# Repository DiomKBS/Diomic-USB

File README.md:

# Diomic-USB
A microphone for all the audiophiles

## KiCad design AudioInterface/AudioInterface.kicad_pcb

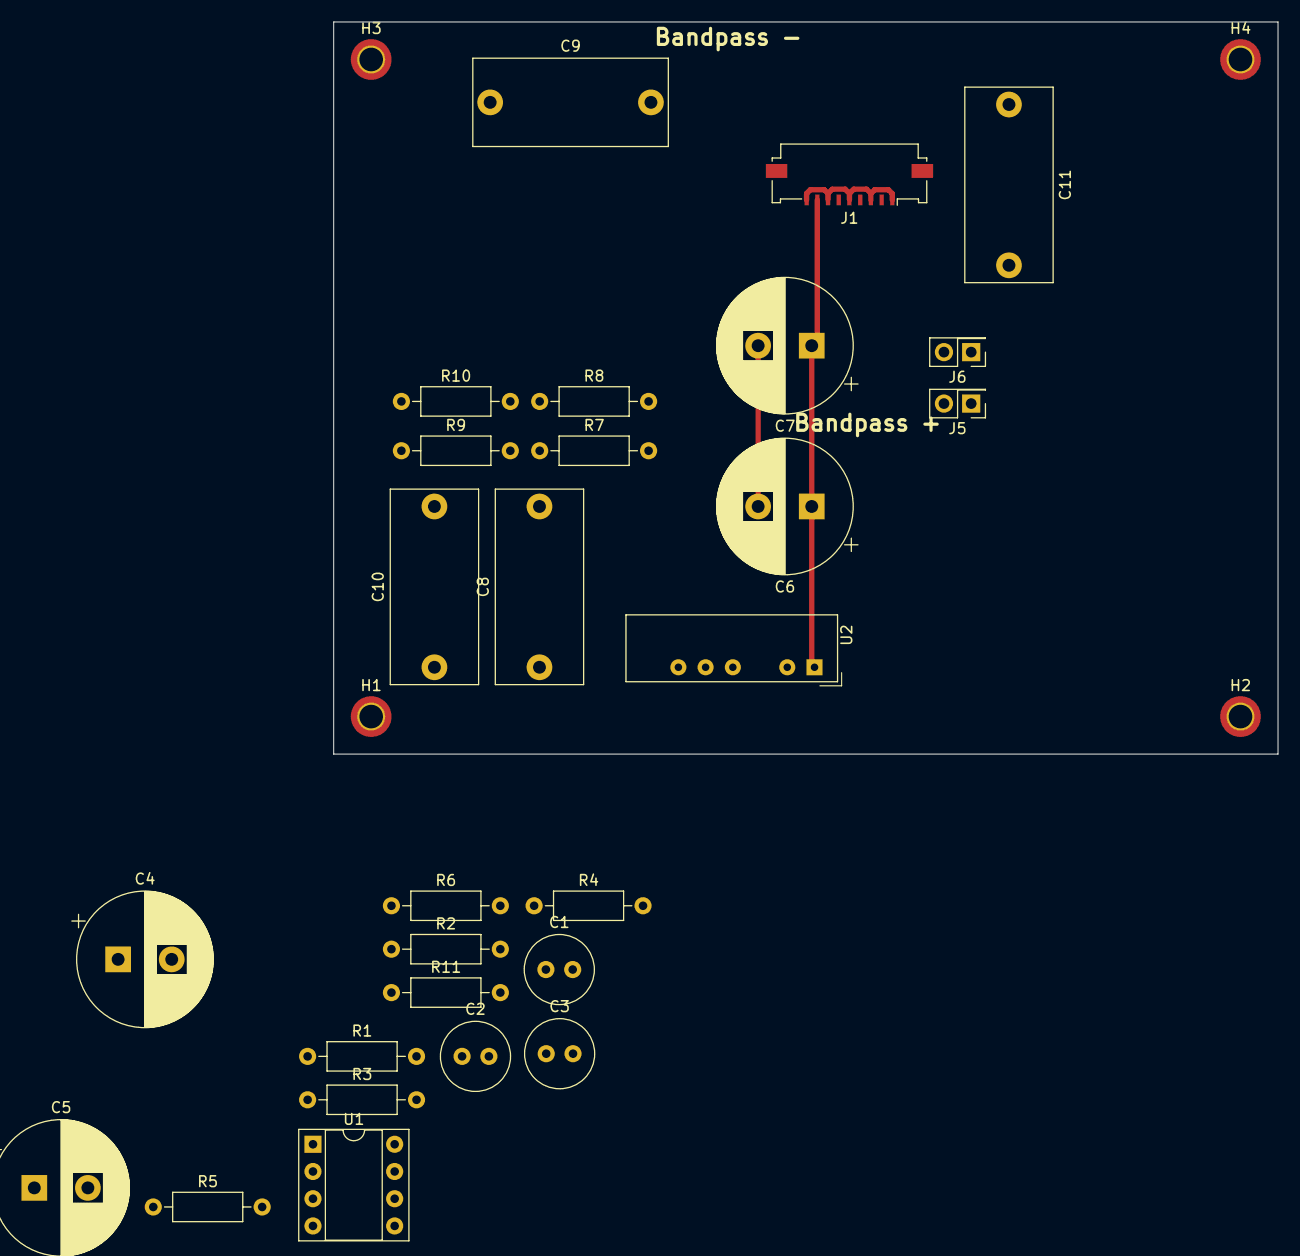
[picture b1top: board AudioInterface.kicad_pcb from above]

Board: 2 copper layers, 88.1 x 68.3 mm, 31 parts (0 on the bottom side), 18 nets.

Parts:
C1, C2, C3: 22u; C_Radial_D6.3mm_H11.0mm_P2.50mm
C4, C5, C6, C7: 2200u; CP_Radial_D12.5mm_P5.00mm
C8, C10: 270nF; C_Rect_L18.0mm_W8.0mm_P15.00mm_FKS3_FKP3
C9, C11: 470pF; C_Rect_L18.0mm_W8.0mm_P15.00mm_FKS3_FKP3
H1, H2, H3, H4: MountingHole_Pad; MountingHole_2.2mm_M2_DIN965_Pad_TopBottom
J1: AudioAmp; Molex_200528-0090_1x09-1MP_P1.00mm_Horizontal
J5, J6: Conn_02x01_Row_Letter_First; PinHeader_2x01_P2.54mm_Vertical
R1, R2, R5, R6: 2.2k; R_Axial_DIN0207_L6.3mm_D2.5mm_P10.16mm_Horizontal
R3, R4: 3.9k; R_Axial_DIN0207_L6.3mm_D2.5mm_P10.16mm_Horizontal
R7, R8, R9, R10: 20k; R_Axial_DIN0207_L6.3mm_D2.5mm_P10.16mm_Horizontal
R11: 5; R_Axial_DIN0207_L6.3mm_D2.5mm_P10.16mm_Horizontal
U1: THAT1512; DIP-8_W7.62mm_Socket
U2: NMA0515SC; Converter_DCDC_Murata_NMAxxxxSC_THT

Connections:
/Bandpass+/B_IN: C8.1, J5.a1, U2.6 (VOUT+)
/Bandpass+/B_OUT: C4.1, C9.2, J5.b1, R1.1, R5.1, R8.2, U1.7 (V+)
/Bandpass-/B_IN: C10.1, J6.a1, U2.4 (VOUT-)
/Bandpass-/B_OUT: C5.2, C11.2, J6.b1, R2.2, R6.2, R10.2, U1.4 (V-)
Audio_out: C3.1, J1.6
GND: C6.2, C7.2, J1.1, J1.3, J1.5, J1.7, J1.9, U2.2 (VIN-)
INT_GND: C4.2, C5.1, C9.1, C11.1, R3.1, R4.2, R5.2, R6.1, R7.2, R9.2, U1.5 (Ref), U2.5 (0V)
unnamed: C1.2, R3.2, U1.2 (-IN)
unnamed: C2.1, R4.1, U1.3 (+IN)
unnamed: C3.2, U1.6 (Out)
unnamed: C8.2, R7.1, R8.1
unnamed: C10.2, R9.1, R10.1
unnamed: R11.1, U1.8 (Rg2)
unnamed: R11.2, U1.1 (Rg1)
Shield: H1.1, H2.1, H3.1, H4.1
VBUS: C6.1, C7.1, J1.8, U2.1 (VIN+)
mic +: C2.2, J1.2, R2.1
mic -: C1.1, J1.4, R1.2

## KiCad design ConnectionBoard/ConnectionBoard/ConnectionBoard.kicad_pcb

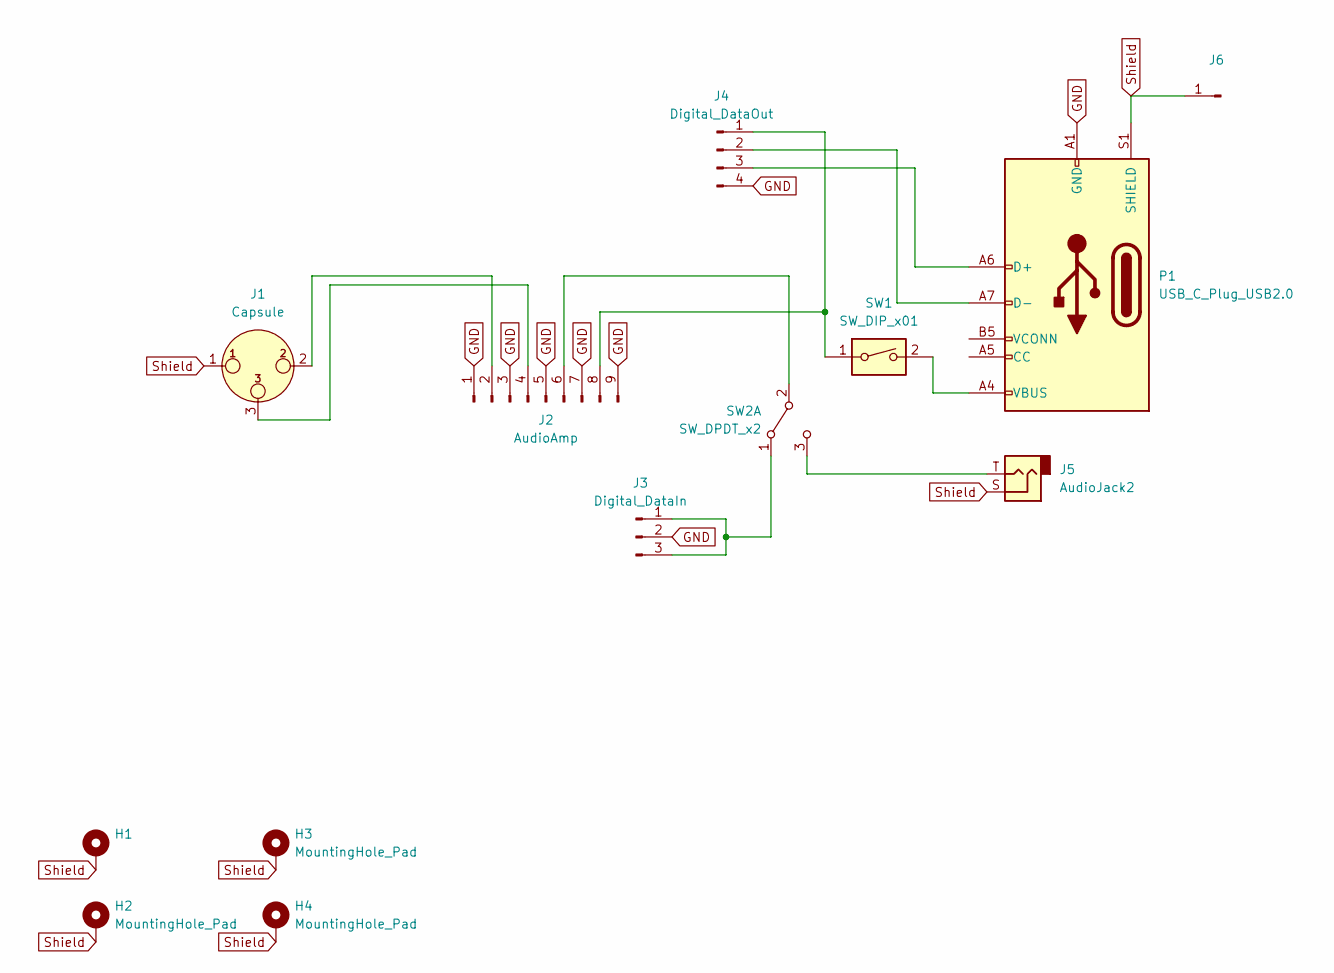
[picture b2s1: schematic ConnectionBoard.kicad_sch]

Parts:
H1: (no value)
H2, H3, H4: MountingHole_Pad
J1: Capsule; Jack_XLR_Neutrik_NC3FBH1_Horizontal
J2: AudioAmp; Molex_200528-0090_1x09-1MP_P1.00mm_Horizontal
J3: Digital_DataIn; Molex_200528-0040_1x04-1MP_P1.00mm_Horizontal
J4: Digital_DataOut; Molex_200528-0040_1x04-1MP_P1.00mm_Horizontal
J5: AudioJack2; TRRS-PJ-320A
J6: (no value)
P1: USB_C_Plug_USB2.0; USB_C_Receptacle_HRO_TYPE-C-31-M-12
SW1: SW_DIP_x01; SW_E-Switch_EG1271_DPDT
SW2: SW_DPDT_x2; switch_lever

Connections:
GND: J2.1, J2.3, J2.5, J2.7, J2.9, J3.2, J4.4, P1.A1 (GND), P1.A12 (GND), P1.B1 (GND), P1.B12 (GND)
unnamed: J1.2, J2.2
unnamed: J1.3, J2.4
unnamed: J2.6, SW2.2 (B)
unnamed: J2.8, J4.1, SW1.1
unnamed: J3.1, J3.3, SW2.1 (A)
unnamed: J4.2, P1.A7 (D-)
unnamed: J4.3, P1.A6 (D+)
unnamed: J5.T, SW2.3 (C)
unnamed: P1.A4 (VBUS), P1.A9 (VBUS), P1.B4 (VBUS), P1.B9 (VBUS), SW1.2
Shield: H1.1, H2.1, H3.1, H4.1, J1.1, J5.S, J6.1, P1.S1 (SHIELD)

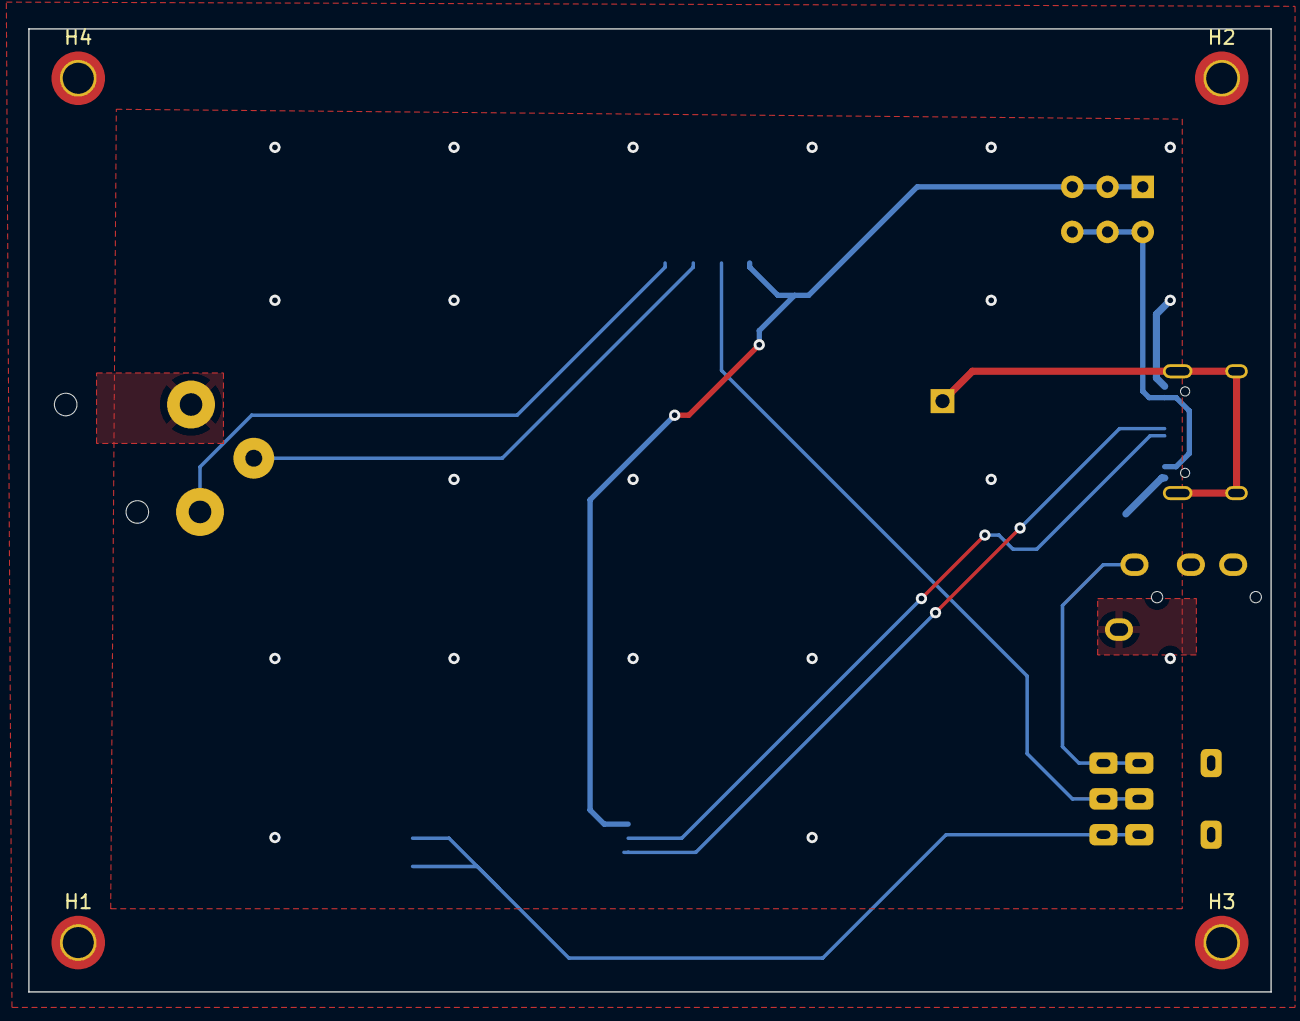
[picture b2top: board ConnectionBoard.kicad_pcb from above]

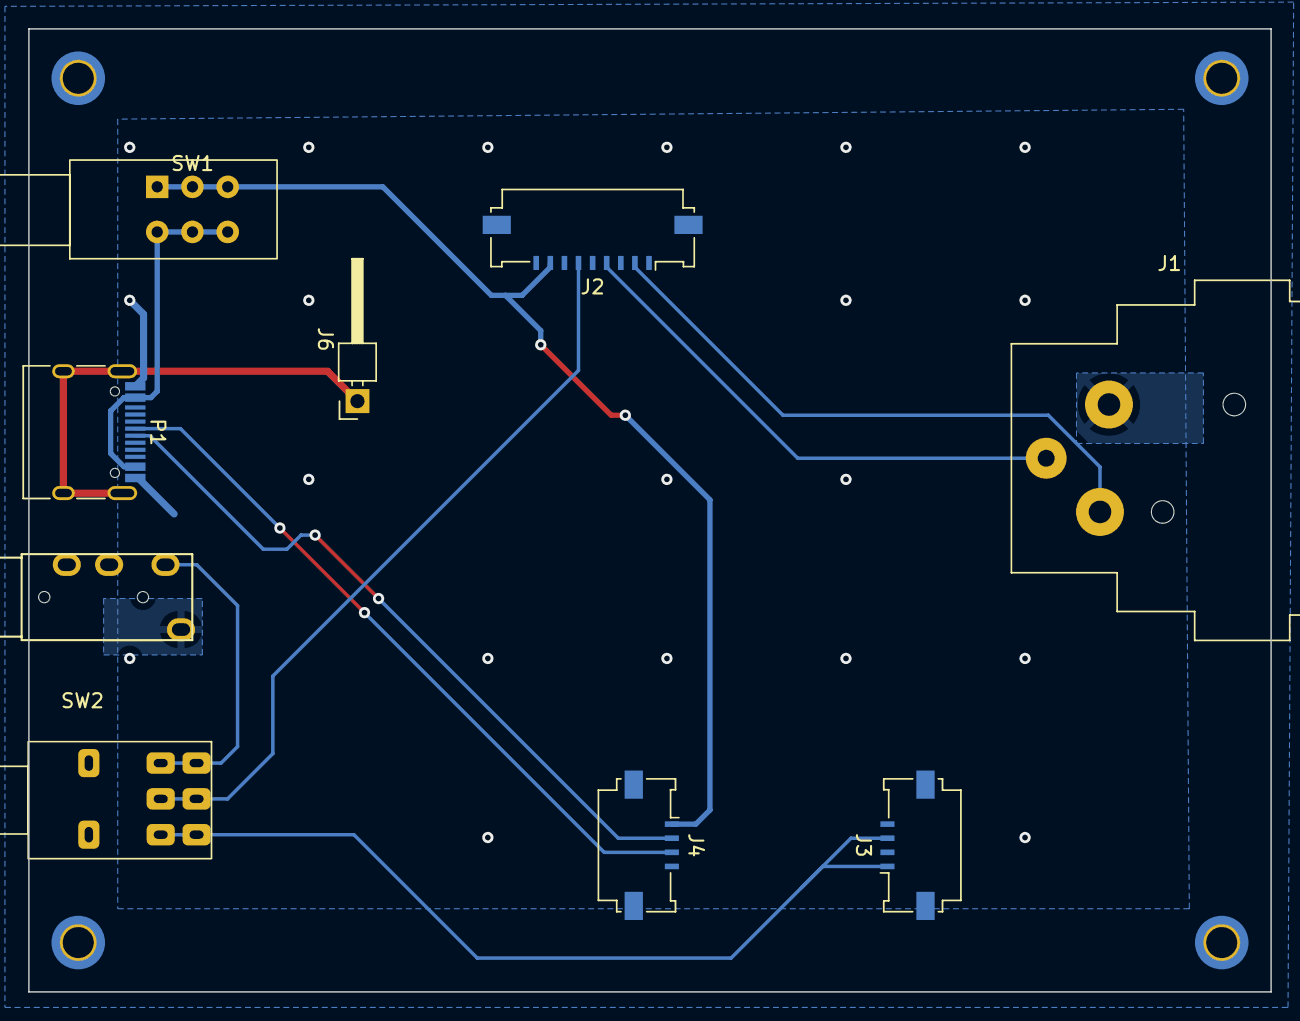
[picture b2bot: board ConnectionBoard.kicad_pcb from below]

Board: 2 copper layers, 88.1 x 68.3 mm, 13 parts (9 on the bottom side), 11 nets.

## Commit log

2022-04-24 inti
2022-04-25 finished pcb
2022-04-25 some adjusments
2022-04-25 image
2022-04-30 new start
